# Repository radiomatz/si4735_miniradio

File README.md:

# si4735_miniradio
SI4735-D60 Circuit and Arduino Sketech for Building a SW/FM Radio with 150kHz..30MHz AM/SSB + 64-108MHz FM

### used Hardware
- Atmega 328P-PU with its internal 8 MHz
- SI4735-D60-GU
- LM386 Dip
- LM1117 3.3 Volts
- SMD Capacitors all 0805
- Elkos all tht, mnost low profile or layed flat
- Quartz 32k Clock Crystal

### Software needed
- Arduino Studio Version 2
- addon for MiniCore (support for single 328 Chips)
- tiny4k oled library and (6x8) font package

### some details
- i am using a 7.2V LiPo, which is directly connencted to the lm386 - it can have about 5-12V
- the mcu and the radio chip SI4735-D60-GU is driven with a LM1117-3.3 with 3.3V, that is important for the SI4735, and enough for an ATMEGA328

### some modifications (which will be in v2 circuit) are made after this circuit(v1):

- add a reset knob between pin 1 of atmega328-pu and gnd for programming from outside.
- insert a 1k2 resistor between pin 1 of lm386 and the 10µ c at pin 8, because gain of 50 is enough.
- my first circuit (the one with the case) i used sockets and plugs for programming outside, but i recommend to solder the AT328 directly and dont use the plugs on the circuit, instead use direct wires for getting more place in the case. Also i used another CA5 

### hints for using
- left button is "down", middle button is "mode", right button is "up"
- you have a preview of the mode right of the mode which has the star in front.
- frequency display has as suffix its step with a slash, also bfo 
- to lock, press up or down in lock mode; to unlock, use up and down simultaneous

if you have any questions, feel free to ask me: dm2hr@darc.de

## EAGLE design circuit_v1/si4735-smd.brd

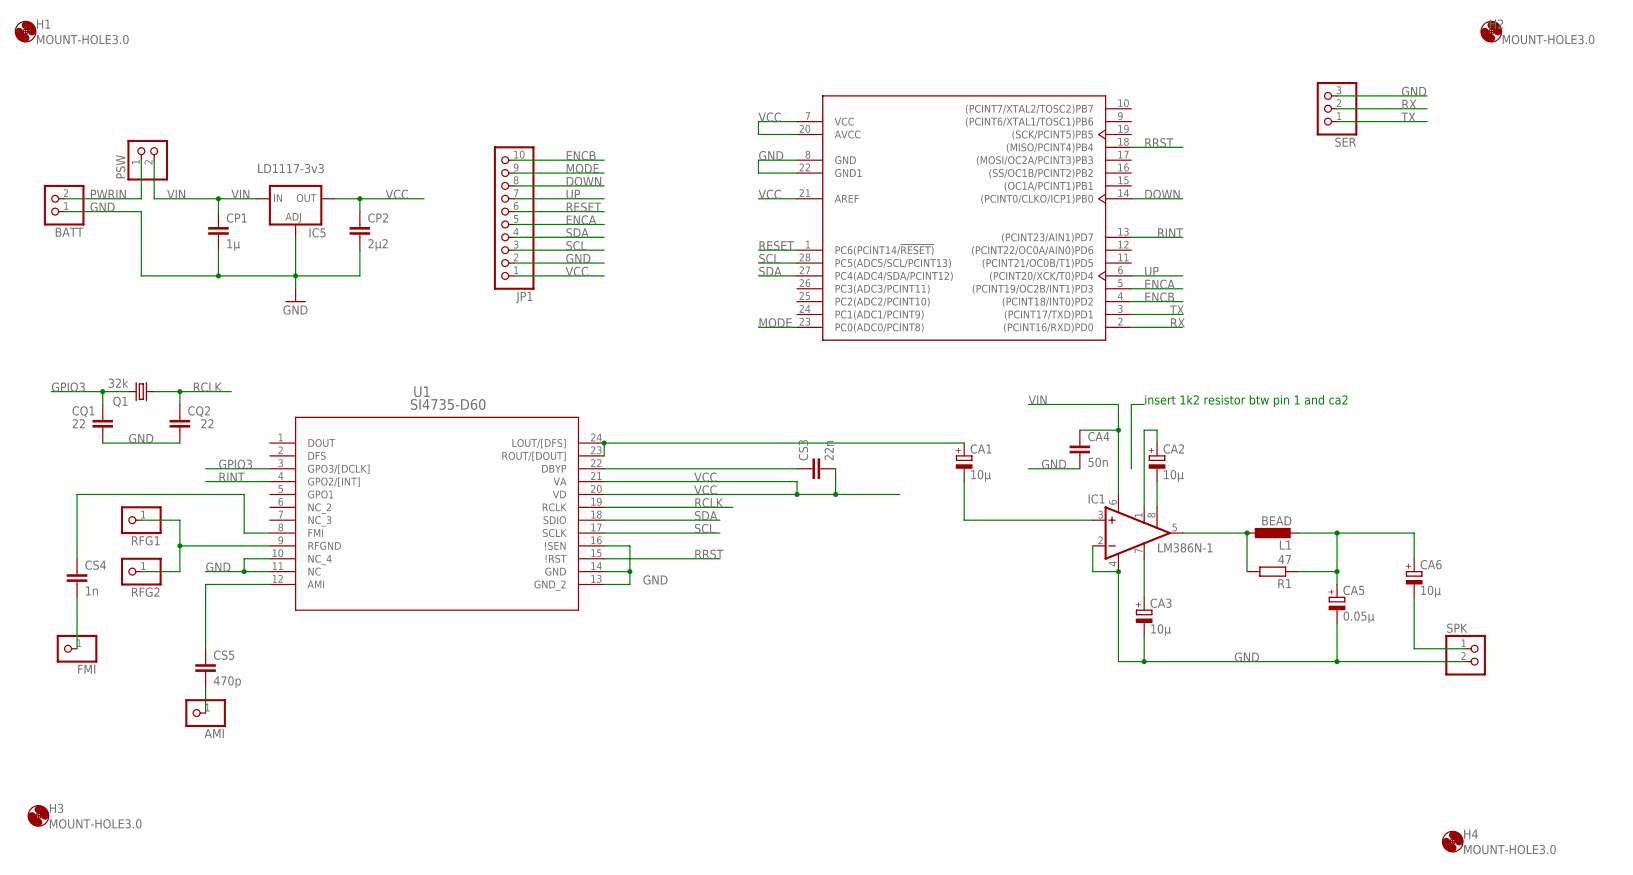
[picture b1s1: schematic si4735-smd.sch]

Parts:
AMI: PINHD-1X1; 1X01
BATT: PINHD-1X2; 1X02
CA1, CA2, CA3, CA6: 10µ; E2,5-6
CA4: 50n; C0805
CA5: 0.05µ; E2,5-6
CP1: 1µ; C0805
CP2: 2µ2; C0805
CQ1, CQ2: 22; C0805
CS3: 22n; C0805
CS4: 1n; C0805
CS5: 470p; C0805
FMI: PINHD-1X1; 1X01
H1, H2, H3, H4: MOUNT-HOLE3.0; 3,0
IC1: LM386N-1; DIL08
IC5: LD1117-3v3; SOT223
JP1: PINHD-1X10; 1X10
L1: BEAD; 0204/7
PSW: PINHD-1X2; 1X02
Q1: 32k; TC26H
R1: 47; M0805
RFG1, RFG2: PINHD-1X1; 1X01
SER: PINHD-1X3; 1X03
SPK: PINHD-1X2; 1X02
U1: SI4735-D60; SSOP24_SIL-M
U3: ATMEGA328P-PU; DIP-28

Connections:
DOWN: JP1.8, U3.14 ((PCINT0/CLKO/ICP1)PB0)
ENCA: JP1.5, U3.5 ((PCINT19/OC2B/INT1)PD3)
ENCB: JP1.10, U3.4 ((PCINT18/INT0)PD2)
GND: BATT.1, CA3.-, CA4.2, CA5.-, CP1.2, CP2.2, CQ1.2, CQ2.2, IC1.2 (-IN), IC1.4 (GND), IC5.1 (ADJ), JP1.2, SER.3, SPK.2, U1.10 (NC_4), U1.11 (NC), U1.13 (GND_2), U1.14 (GND), U1.16 (\!SEN), U3.8 (GND), U3.22 (GND1)
GPIO3: CQ1.1, Q1.2, U1.3 (GPO3/[DCLK])
MODE: JP1.9, U3.23 (PC0(ADC0/PCINT8))
unnamed: CA1.+, U1.23 (ROUT/[DOUT]), U1.24 (LOUT/[DFS])
unnamed: CA1.-, IC1.3 (+IN)
unnamed: CA2.+, IC1.1 (GAIN)
unnamed: CA2.-, IC1.8 (GAIN)
unnamed: IC1.5 (OUT), L1.1, R1.2
unnamed: CA5.+, CA6.+, L1.2, R1.1
unnamed: CA6.-, SPK.1
unnamed: CA3.+, IC1.7 (BYPASS)
unnamed: RFG1.1, RFG2.1, U1.9 (RFGND)
unnamed: CS4.1, U1.8 (FMI)
unnamed: CS4.2, FMI.1
unnamed: CS3.1, U1.22 (DBYP)
unnamed: CS5.1, U1.12 (AMI)
unnamed: AMI.1, CS5.2
PWRIN: BATT.2, PSW.1
RCLK: CQ2.1, Q1.1, U1.19 (RCLK)
RESET: JP1.6, U3.1 (PC6(PCINT14/!RESET))
RINT: U1.4 (GPO2/[INT]), U3.13 ((PCINT23/AIN1)PD7)
RRST: U1.15 (\!RST), U3.18 ((MISO/PCINT4)PB4)
RX: SER.2, U3.2 ((PCINT16/RXD)PD0)
SCL: JP1.3, U1.17 (SCLK), U3.28 (PC5(ADC5/SCL/PCINT13))
SDA: JP1.4, U1.18 (SDIO), U3.27 (PC4(ADC4/SDA/PCINT12))
TX: SER.1, U3.3 ((PCINT17/TXD)PD1)
UP: JP1.7, U3.6 ((PCINT20/XCK/T0)PD4)
VCC: CP2.1, CS3.2, IC5.4 (OUT), JP1.1, U1.20 (VD), U1.21 (VA), U3.7 (VCC), U3.20 (AVCC), U3.21 (AREF)
VIN: CA4.1, CP1.1, IC1.6 (VS), IC5.3 (IN), PSW.2

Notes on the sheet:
insert 1k2 resistor btw pin 1 and ca2

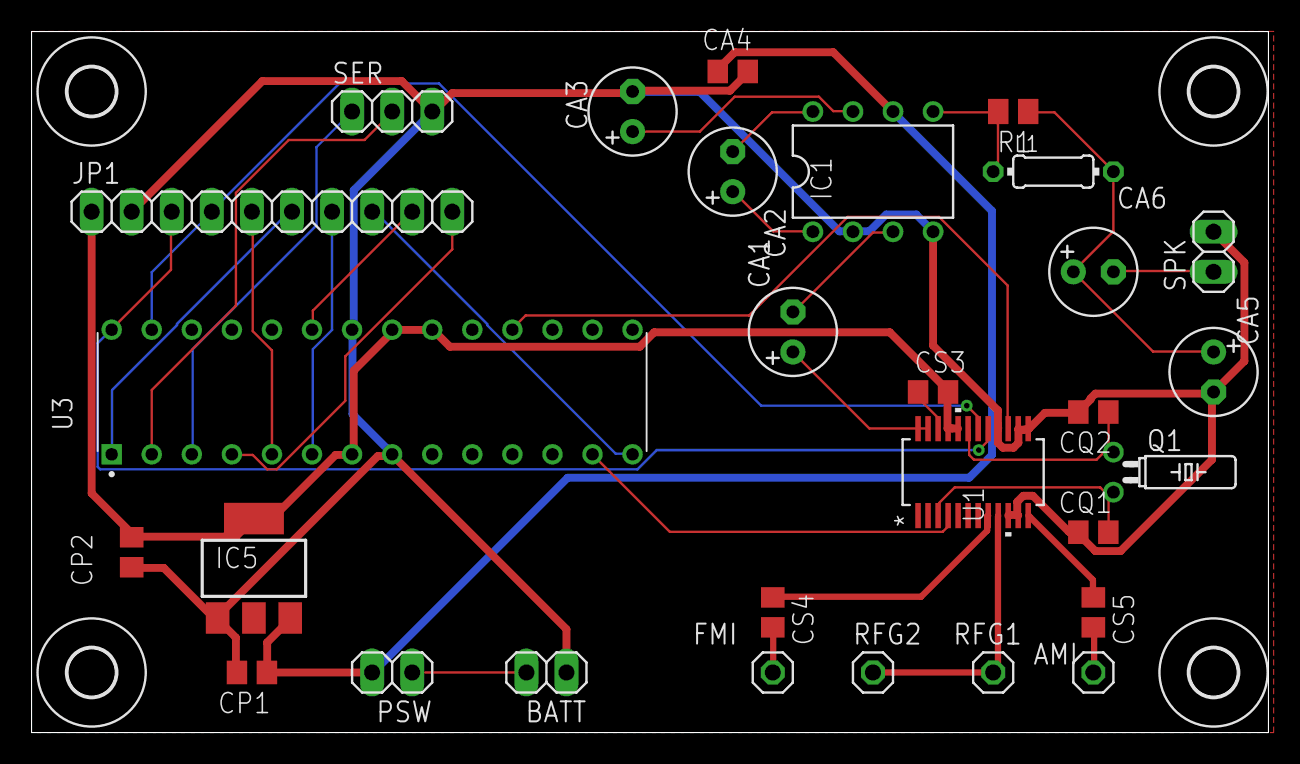
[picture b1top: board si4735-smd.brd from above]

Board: 2 copper layers, 78.4 x 44.4 mm, 33 parts (0 on the bottom side), 32 nets.

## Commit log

2026-04-27 added: documentation for hardware and software
2026-04-27 added: hexfile for eeprommer
